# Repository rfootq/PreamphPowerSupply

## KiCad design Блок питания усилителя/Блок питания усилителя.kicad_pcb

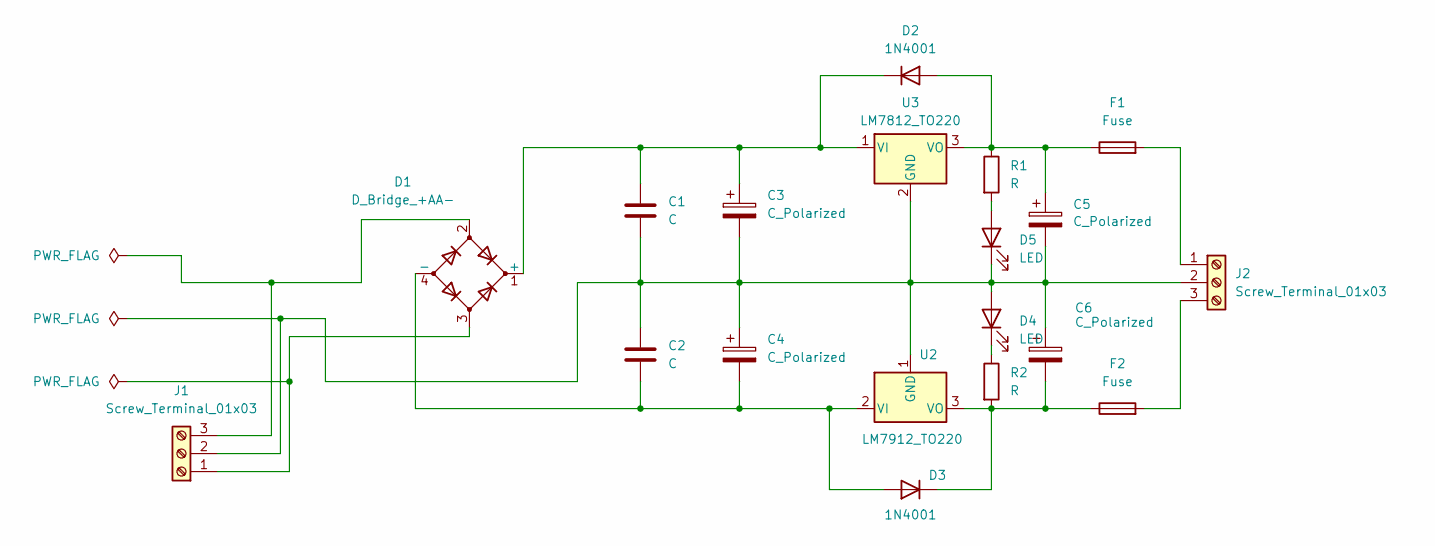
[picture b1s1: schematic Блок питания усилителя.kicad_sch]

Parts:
C1, C2: C; C_Disc_D7.5mm_W5.0mm_P10.00mm
C3, C4: C_Polarized; CP_Radial_D16.0mm_P7.50mm
C5, C6: C_Polarized; CP_Radial_D8.0mm_P3.50mm
D1: D_Bridge_+AA-; Diode_Bridge_Vishay_KBL
D2, D3: 1N4001; D_DO-41_SOD81_P10.16mm_Horizontal
D4, D5: LED; LED_D3.0mm
F1: Fuse; Fuseholder_Clip-5x20mm_Littelfuse_445-030_Inline_P20.50x5.2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
F2: Fuse; Fuseholder_Clip-5x20mm_Littelfuse_520_Inline_P20.50x5.80mm_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
J1, J2: Screw_Terminal_01x03; TerminalBlock_Altech_AK300-3_P5.00mm
R1, R2: R; R_Axial_DIN0207_L6.3mm_D2.5mm_P7.62mm_Horizontal
U2: LM7912_TO220; TO-220-3_Vertical
U3: LM7812_TO220; TO-220-3_Vertical

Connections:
unnamed: C1.1, C3.1, D1.1 (+), D2.1 (K), U3.1 (VI)
unnamed: C2.2, C4.2, D1.4 (-), D3.2 (A), U2.2 (VI)
unnamed: C5.1, D2.2 (A), F1.1, R1.1, U3.3 (VO)
unnamed: C6.2, D3.1 (K), F2.1, R2.2, U2.3 (VO)
unnamed: C1.2, C2.1, C3.2, C4.1, C5.2, C6.1, D4.2 (A), D5.1 (K), J1.2, J2.2, U2.1 (GND), U3.2 (GND)
unnamed: D4.1 (K), R2.1
unnamed: D5.2 (A), R1.2
unnamed: D1.3, J1.1
unnamed: D1.2, J1.3
unnamed: F1.2, J2.1
unnamed: F2.2, J2.3

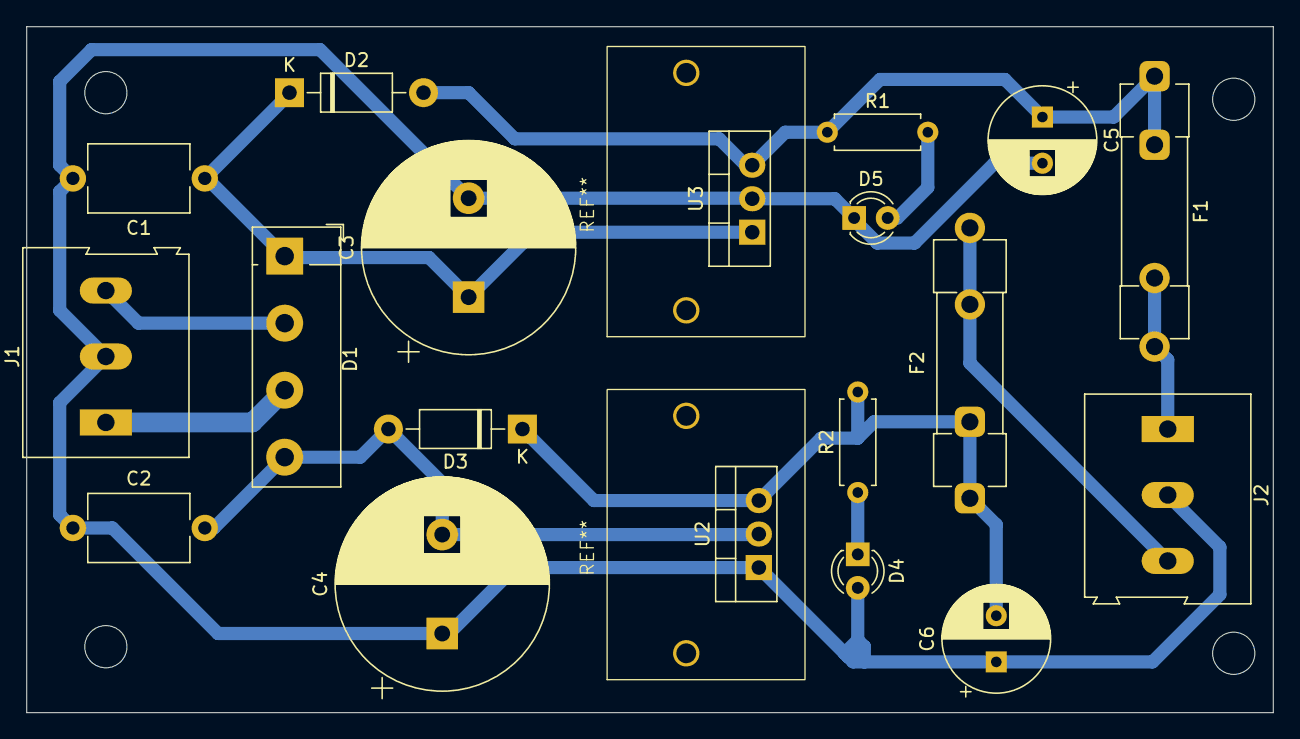
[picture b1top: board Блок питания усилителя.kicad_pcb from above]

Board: 2 copper layers, 94.5 x 52.0 mm, 19 parts (0 on the bottom side), 11 nets.

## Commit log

2024-07-17 Первый коммит
2024-07-19 Более менее рабчая версия платы
2024-07-22 Перенос данных на новую ветку, и добавлены параметры игнора
2024-07-26 Окончанительная версия платы. Без логотипа
